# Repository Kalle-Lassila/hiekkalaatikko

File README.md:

# hiekkalaatikko
Sandbox for various suffs.
It is likely that nothing in this repository is useful.

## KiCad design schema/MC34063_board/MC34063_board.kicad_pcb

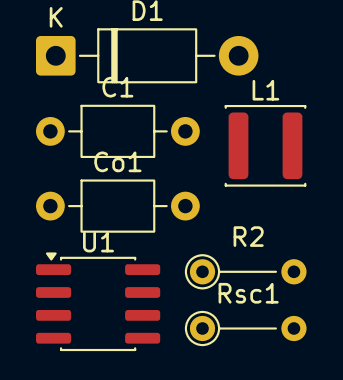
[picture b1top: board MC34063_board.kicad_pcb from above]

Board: 2 copper layers, 7 parts (0 on the bottom side), 6 nets, no tracks yet.

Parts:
C1: 100uF; C_Axial_L3.8mm_D2.6mm_P7.50mm_Horizontal
Co1: 470uF; C_Axial_L3.8mm_D2.6mm_P7.50mm_Horizontal
D1: 1N4001; D_DO-41_SOD81_P10.16mm_Horizontal
L1: 220uH; L_Pulse_PA4332
R2: 3,6k; R_Axial_DIN0204_L3.6mm_D1.6mm_P5.08mm_Vertical
Rsc1: 0,33; R_Axial_DIN0204_L3.6mm_D1.6mm_P5.08mm_Vertical
U1: MC34063AP; SOIC-8_3.9x4.9mm_P1.27mm

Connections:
GND: C1.2, Co1.2, D1.2 (A), U1.4 (GND)
unnamed: Co1.1, L1.2, R2.2
unnamed: D1.1 (K), L1.1, U1.2 (SwE)
unnamed: Rsc1.2, U1.1 (SwC), U1.7 (Ipk), U1.8 (DC)
unnamed: R2.1, U1.5 (Vfb)
VCC: C1.1, Rsc1.1, U1.6 (Vin)

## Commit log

2024-02-15 Added some scribble on Linux.
2024-02-18 Scribble
2024-02-20 Poked at snprintf and dtostrf on avr
2024-02-25 3D model
    For organizer tray shelves.
2024-02-25 Added bar mount model to hold bar in-place.
2024-02-25 Added humidity display.
2024-03-03 Random 3D models
    Made for whatever purpose
2024-03-10 Updated tray shelves
    Made it simpler to find right settings
2024-09-19 New model for belt sander for knife making.
    Initial untested models
2024-10-23 Belt sander guide v2
    and knife seath parts.
2024-12-28 New seath insert
2025-08-16 Diamond plate holder
2025-08-17 Updated plate holder
2025-08-17 First iteration of tin can lid model
2025-08-19 Updated dimensions
2025-08-19 Updated tolerances
2025-08-28 Proper sizing for 100_5mm lid.
2025-08-28 Model for 100_5mm lid.
2025-09-15 Added gear selector spacer
2025-09-23 Screw on caps
2025-10-09 Models and schemas
2025-10-09 Additional models
2025-10-09 Organization
2025-10-09 Simulation and updates for smps board
2025-10-16 Schema updates
2025-12-09 Various 3D models and such
2025-12-09 Started modelling socet holders
2025-12-09 TEST PRINT V1 socket organizer
2025-12-10 Added camfer and decreased 10-17mm socket tolerances by .5mm to 22.5mm
2025-12-10 Added base for 23-34mm sockets
2026-01-03 Misc. models
2026-01-04 PWR socket organizer base
2026-01-05 pwr_socket_V!
2026-01-06 Violin back clamp initial commit
2026-01-06 Look at previous commit
2026-01-06 pwr_socket_V2
2026-01-07 Violin back clamp additional parts
2026-01-08 First layer calibration model
    And parts for Volvo
2026-01-11 Holder models for 3/8 sockets and alloy wheel lug nut sockets
2026-01-14 1/4in socket set base model
2026-01-19 More luthier tool models
2026-01-20 Violin string lifter V1
2026-01-21 Updated string lifter dimensions
2026-01-28 Violin string lifter V2
2026-02-04 New models
2026-03-17 New models and cleanup
    Belt sander guide, volvo upper torque mount
2026-04-14 New model
2026-05-17 Volvo lower torque mount frame side
